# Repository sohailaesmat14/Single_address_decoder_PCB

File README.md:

# Single Address Decoder PCB Circuit

## Overview:

This project features a Single Address Decoder PCB Circuit, designed to decode a specific address and activate a corresponding output. It's commonly used in digital electronics for memory addressing, bus systems, and other applications requiring selective activation based on an address input.

## Components:

1. Printed Circuit Board (PCB)
2. Integrated Circuits (ICs)
3. Resistors
4. Capacitors
5. LEDs (Light Emitting Diodes)
6. Header pins
7. Power source (battery)

## Setup:

1. **Hardware:**
   - Assemble the components according to the PCB layout and schematic diagram.
   - Solder the components onto the PCB, ensuring correct polarity and connections.
   - Connect the power source to the PCB.

2. **Software:**
   - Eagle Software.

## Usage:

1. Apply power to the circuit.
2. Input the desired address to the address pins.
3. The corresponding output LED will be activated if the input address matches the decoder's programmed address.
4. Test different addresses to verify the functionality of the decoder circuit.

## PCB Design:

## Notes:

- Double-check the connections and soldering to ensure there are no short circuits or open connections.
- Verify the functionality of the decoder circuit with different address inputs.
- Customize the PCB layout and components according to your specific requirements.

## Author:

Sohaila Esmat

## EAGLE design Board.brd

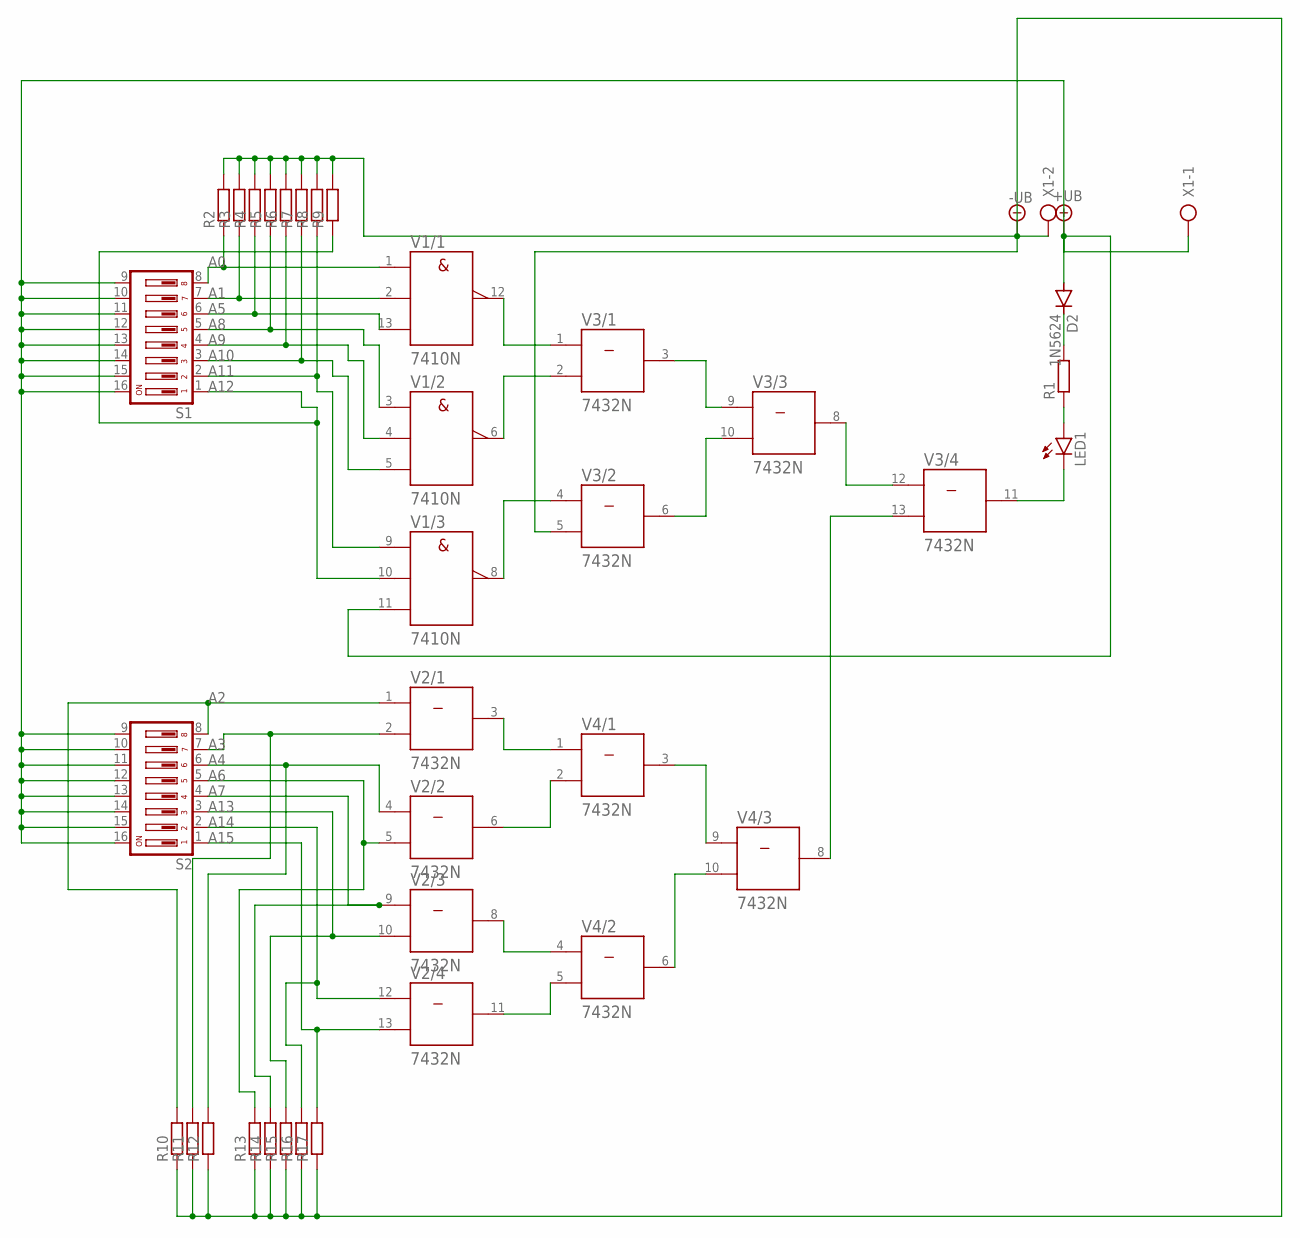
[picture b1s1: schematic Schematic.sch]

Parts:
D2: 1N5624; DO201-15
LED1: LED5MM
R1, R2, R3, R4, R5, R6, R7, R8, R9, R10, R11, R12, R13, R14, R15, R16, R17: R-EU_0207/10; 0207/10
S1, S2: SD4-08
V1: 7410N; DIL14
V2, V3, V4: 7432N; DIL14
X1: AK500/2

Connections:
+UB: D2.A, S1.9, S1.10, S1.11, S1.12, S1.13, S1.14, S1.15, S1.16, S2.9, S2.10, S2.11, S2.12, S2.13, S2.14, S2.15, S2.16, V1.11 (C), V1.14 (+UB), V2.14 (+UB), V3.14 (+UB), V4.14 (+UB), X1.1
-UB: R2.2, R3.2, R4.2, R5.2, R6.2, R7.2, R8.2, R9.2, R10.1, R11.1, R12.1, R13.1, R14.1, R15.1, R16.1, R17.1, V1.7 (-UB), V2.7 (-UB), V3.5 (B), V3.7 (-UB), V4.7 (-UB), X1.2
A0: R2.1, S1.8, V1.1 (A)
A1: R3.1, S1.7, V1.2 (B)
A2: R10.2, S2.8, V2.1 (A)
A3: R11.2, S2.7, V2.2 (B)
A4: R12.2, S2.6, V2.4 (A)
A5: R4.1, S1.6, V1.13 (C)
A6: R13.2, S2.5, V2.5 (B)
A7: R14.2, S2.4, V2.9 (A)
A8: R5.1, S1.5, V1.3 (A)
A9: R6.1, S1.4, V1.4 (B)
A10: R7.1, S1.3, V1.5 (C)
A11: R8.1, S1.2, V1.9 (A)
A12: R9.1, S1.1, V1.10 (B)
A13: R15.2, S2.3, V2.10 (B)
A14: R16.2, S2.2, V2.12 (A)
A15: R17.2, S2.1, V2.13 (B)
unnamed: LED1.K (C), V3.11 (Y)
unnamed: LED1.A, R1.1
unnamed: D2.C, R1.2
unnamed: V2.3 (Y), V4.1 (A)
unnamed: V2.6 (Y), V4.2 (B)
unnamed: V2.8 (Y), V4.4 (A)
unnamed: V2.11 (Y), V4.5 (B)
unnamed: V4.3 (Y), V4.9 (A)
unnamed: V4.6 (Y), V4.10 (B)
unnamed: V1.12 (Y), V3.1 (A)
unnamed: V1.6 (Y), V3.2 (B)
unnamed: V1.8 (Y), V3.4 (A)
unnamed: V3.3 (Y), V3.9 (A)
unnamed: V3.6 (Y), V3.10 (B)
unnamed: V3.8 (Y), V3.12 (A)
unnamed: V3.13 (B), V4.8 (Y)

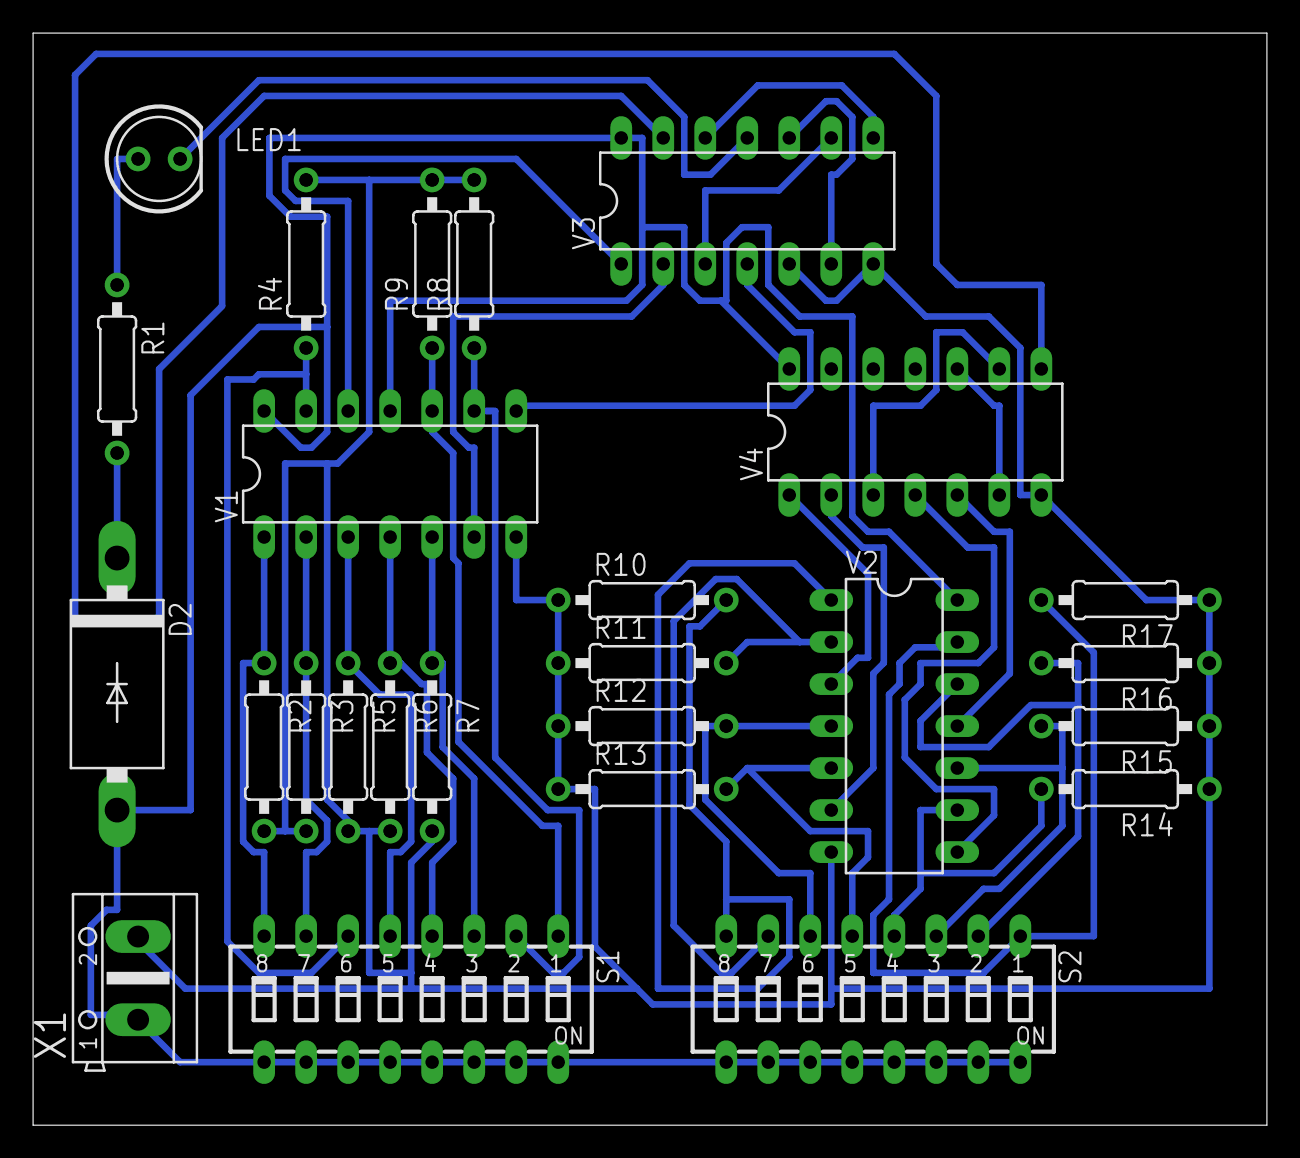
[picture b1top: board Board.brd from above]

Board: 2 copper layers, 74.6 x 66.0 mm, 26 parts (0 on the bottom side), 34 nets.
